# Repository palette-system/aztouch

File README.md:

# AZTOUCH (ミニトラックパッド)

<table><tr><td>
<br>
<br>
</td><td>

</td></tr></table>

<br><br>

## 接続方法

<br><br>

## 基本情報

<br>

電圧： 3V～5V<br>
消費電力： 1.7mA～2mA<br>
サイズ： 幅：25mm 高さ：21mm 厚さ：1mm<br>
I2Cアドレス：0x0A(固定)<br>

<br>
※ 電池駆動推薦、電源が安定しないと動作が不安定になる場合があります。<br>

<br><br>

## コマンド

<table>
  <tr>
    <th>コマンド</th>
    <th>内容</th>
  </tr>
  <tr>
    <td>0x30</td>
    <td>
    <b>設定値要求</b><br>
    このコマンドを送った次にデータリクエストが来た時に、1度だけ下記の7バイトのレスポンスになる。<br>
    [<br>
    　0x23(固定),<br>
    　マウススピード設定(0x00 ～ 0x04),<br>
    　drag_touch_time_max,<br>
    　drag_interval_time_max,<br>
    　tap_touch_time_max,<br>
    　move_touch_time_start,<br>
    　read_wait_time<br>
    ]<br>
    <br>
    コマンド例：[0x30]
    </td>
  </tr>
  <tr>
    <td>0x40</td>
    <td>
    <b>マウスのスピード設定</b><br>
    次に送られてきたバイトで移動速度を設定。<br>
    0x00 ～ 0x04 の間で設定可能<br>
    デフォルト値：0x02<br>
    <br>
    コマンド例：[0x40, 0x01]
    </td>
  </tr>
  <tr>
    <td>0x41</td>
    <td>
    <b>ドラッグ1回目のタッチの最大時間(n / 5ms)</b><br>
    次に送られてきたバイトで <b>drag_touch_time_max</b> の値を設定。<br>
    ※ 1=5ミリ秒、デフォルト値：0x64(500ミリ秒)<br>
    <br>
    コマンド例：[0x41, 0x64]
    </td>
  </tr>
  <tr>
    <td>0x42</td>
    <td>
    <b>ドラッグ2回目のタッチまでの最大時間(n / 5ms)</b><br>
    次に送られてきたバイトで <b>drag_interval_time_max</b> の値を設定。<br>
    ※ 1=5ミリ秒、デフォルト値：0x28(200ミリ秒)<br>
    <br>
    コマンド例：[0x42, 0x28]
    </td>
  </tr>
  <tr>
    <td>0x43</td>
    <td>
    <b>タップのタッチの最大時間(n / 5ms)</b><br>
    次に送られてきたバイトで <b>tap_touch_time_max</b> の値を設定。<br>
    ※ 1=5ミリ秒、デフォルト値：0x14(100ミリ秒)<br>
    <br>
    コマンド例：[0x43, 0x14]
    </td>
  </tr>
  <tr>
    <td>0x44</td>
    <td>
    <b>移動開始するまでの時間(n / 5ms)</b><br>
    次に送られてきたバイトで <b>move_touch_time_start</b> の値を設定。<br>
    ※ 1=5ミリ秒、デフォルト値：0x14(100ミリ秒)<br>
    <br>
    コマンド例：[0x44, 0x14]
    </td>
  </tr>
  <tr>
    <td>0x45</td>
    <td>
    <b>アナログ値取得待ち時間</b><br>
    次に送られてきたバイトで <b>read_wait_time</b> の値を設定。<br>
    ※ デフォルト値：0x28(40 NOP)<br>
    <br>
    コマンド例：[0x45, 0x28]
    </td>
  </tr>
  <tr>
    <td>0x4C</td>
    <td>
    <b>スリープ</b><br>
    AZTOUCHをスリープ状態にします。<br>
    スリープ状態の間消費電力は0.1mAになります。<br>
    I2Cのリクエストが飛ぶとスリープ状態から復帰します。<br>
    <br>
    コマンド例：[0x4C]
    </td>
  </tr>
</table>
※ EEPROM に保存されるため電源を落としても保持されます。<br>

<br><br>

## データレスポンス
AZ1UBALLやPIM447と同じフォーマットで操作情報を取得できます。<br>

<table>
  <tr>
    <th>バイト</th>
    <th>内容</th>
  </tr>
  <tr>
    <td>0x00</td>
    <td>左方向への移動距離</td>
  </tr>
  <tr>
    <td>0x01</td>
    <td>右方向への移動距離</td>
  </tr>
  <tr>
    <td>0x02</td>
    <td>上方向への移動距離</td>
  </tr>
  <tr>
    <td>0x03</td>
    <td>下方向への移動距離</td>
  </tr>
  <tr>
    <td>0x04</td>
    <td>タッチ情報<br>
    下記ビットを足し合わせた数値を返します。<br>
    <br>
    0x01 = 縦に2点タッチしている<br>
    0x02 = 横に2点タッチしている<br>
    0x04 = タッチしている<br>
    0x08 = ドラッグしている<br>
    0x10 = 未使用<br>
    0x20 = 未使用<br>
    0x40 = 2点タップ (右クリック)<br>
    0x80 = 1点タップ (左クリック)<br>
    </td>
  </tr>
</table>

<br><br>

## データ取得フロー
<br>
１．データリクエストを行ったタイミングでタッチ情報を取得するため、リードサイクルを少なくするほど省電力化できます。<br>
２．データリクエストの結果は前のサイクルのタイミングで取得したタッチ情報となります。<br>
３．タッチ情報取得のタイミングは割り込み禁止となるので、その間はI2Cのリクエストを受け取れません。<br>

<br>
<br>
<br>

<br><br>

<b>サイクル間隔と各イベントの感度</b><br>
<table>
  <tr>
    <th>間隔(ミリ秒)</th>
    <th>消費電力(mA)</th>
    <th>移動</th>
    <th>2点タッチ</th>
    <th>タップ</th>
    <th>ダブルタップ</th>
  </tr>
  <tr>
    <td>10</td>
    <td>2.0</td>
    <td>〇</td>
    <td>〇</td>
    <td>〇</td>
    <td>〇</td>
  </tr>
  <tr>
    <td>20</td>
    <td>1.9</td>
    <td>〇</td>
    <td>〇</td>
    <td>〇</td>
    <td>△</td>
  </tr>
  <tr>
    <td>30</td>
    <td>1.8</td>
    <td>〇</td>
    <td>〇</td>
    <td>〇</td>
    <td>△</td>
  </tr>
  <tr>
    <td>40</td>
    <td>1.8</td>
    <td>〇</td>
    <td>〇</td>
    <td>△</td>
    <td>△</td>
  </tr>
  <tr>
    <td>50</td>
    <td>1.8</td>
    <td>〇</td>
    <td>〇</td>
    <td>△</td>
    <td>△</td>
  </tr>
  <tr>
    <td>60</td>
    <td>1.8</td>
    <td>〇</td>
    <td>〇</td>
    <td>△</td>
    <td>△</td>
  </tr>
  <tr>
    <td>70</td>
    <td>1.7</td>
    <td>〇</td>
    <td>〇</td>
    <td>×</td>
    <td>×</td>
  </tr>
  <tr>
    <td>80</td>
    <td>1.7</td>
    <td>△</td>
    <td>△</td>
    <td>×</td>
    <td>×</td>
  </tr>
  <tr>
    <td>90</td>
    <td>1.7</td>
    <td>△</td>
    <td>△</td>
    <td>×</td>
    <td>×</td>
  </tr>
  <tr>
    <td>100</td>
    <td>1.7</td>
    <td>△</td>
    <td>△</td>
    <td>×</td>
    <td>×</td>
  </tr>
</table>

<br><br>

## ピン情報取得フロー
<br>
１．割り込み禁止の間にタッチしているかどうかのアナログ値を取得します。<br>
２．読み込み時の待ち時間を <b>read_wait_time</b> で設定できます。<br>
<br>
<br>
<br>

<br><br>

## アクション設定
<br>
<b>ドラッグ判定</b><br>
<br>

<br>

<b>タップ判定</b><br>
<br>

<br>

<b>マウス移動判定</b><br>
タップの時にマウスが移動してしまわないように、タッチしてから少しの間マウス移動はしないようになっています。<br>
<br>

<br>

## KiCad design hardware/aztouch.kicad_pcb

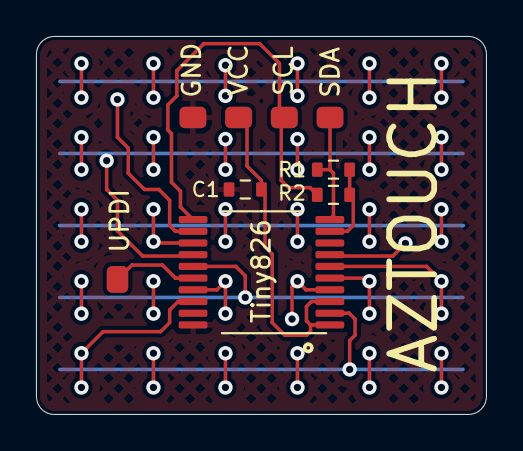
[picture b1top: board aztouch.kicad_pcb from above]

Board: 2 copper layers, 25.0 x 21.0 mm, 4 parts (0 on the bottom side), 5 nets.

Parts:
C1: 1kΩ; R_0805_2012Metric1.2
R1, R2: 1kΩ; R_0805_2012Metric1.2
Tiny826: TSSOP-20_4.4x6.5mm_P0.65mm

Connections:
GND: C1.2, Tiny826.20
OUT1: R1.1, R2.1, Tiny826.9
SCL: R2.2, Tiny826.11
SDA: R1.2, Tiny826.10
VCC: C1.1, Tiny826.1, Tiny826.3

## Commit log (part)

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2026-01-31 add aztouch
2026-01-31 add kicad data
2026-02-02 update firm
2026-02-03 update dorag
2026-02-07 update speed
2026-02-07 speed update
2026-02-13 add epprom
2026-02-13 add sleep
2026-03-22 add firm2
2026-03-24 firm update
2026-03-24 firm2 update
2026-03-30 firmware2 update
2026-04-01 add doc
2026-04-02 update flow image
2026-04-13 update cmmand doc
2026-04-13 add photo
2026-04-13 add connect
2026-06-23 add 9pad trackpad
